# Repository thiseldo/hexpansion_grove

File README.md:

# "Seeed Studio Grove" connector adapter

Enables many of the [Grove expansion modules](https://wiki.seeedstudio.com/Grove_System/) to be used with the badge.

* I2C devices such as sensors
* I/O 1 uses HS_F and HS_G pins
* I/O 2 uses HS_H and HS_I pins

Use of pins is described at [Create a hexpansion](https://tildagon.badge.emfcamp.org/hexpansions/creating-hexpansions/)

# What's included

* kicad - The Kicad project files for the hexpansion along with gerbers ready to send to a PCB fabricator.
* software - Example applications for the hexpansions, using DS18B20 temperature probe and a Grove alcohol gas sensor.

## Acknowledgements

Uses the [hexpansion template from EMF](https://github.com/emfcamp/badge-2024-hardware/tree/main/hexpansion).

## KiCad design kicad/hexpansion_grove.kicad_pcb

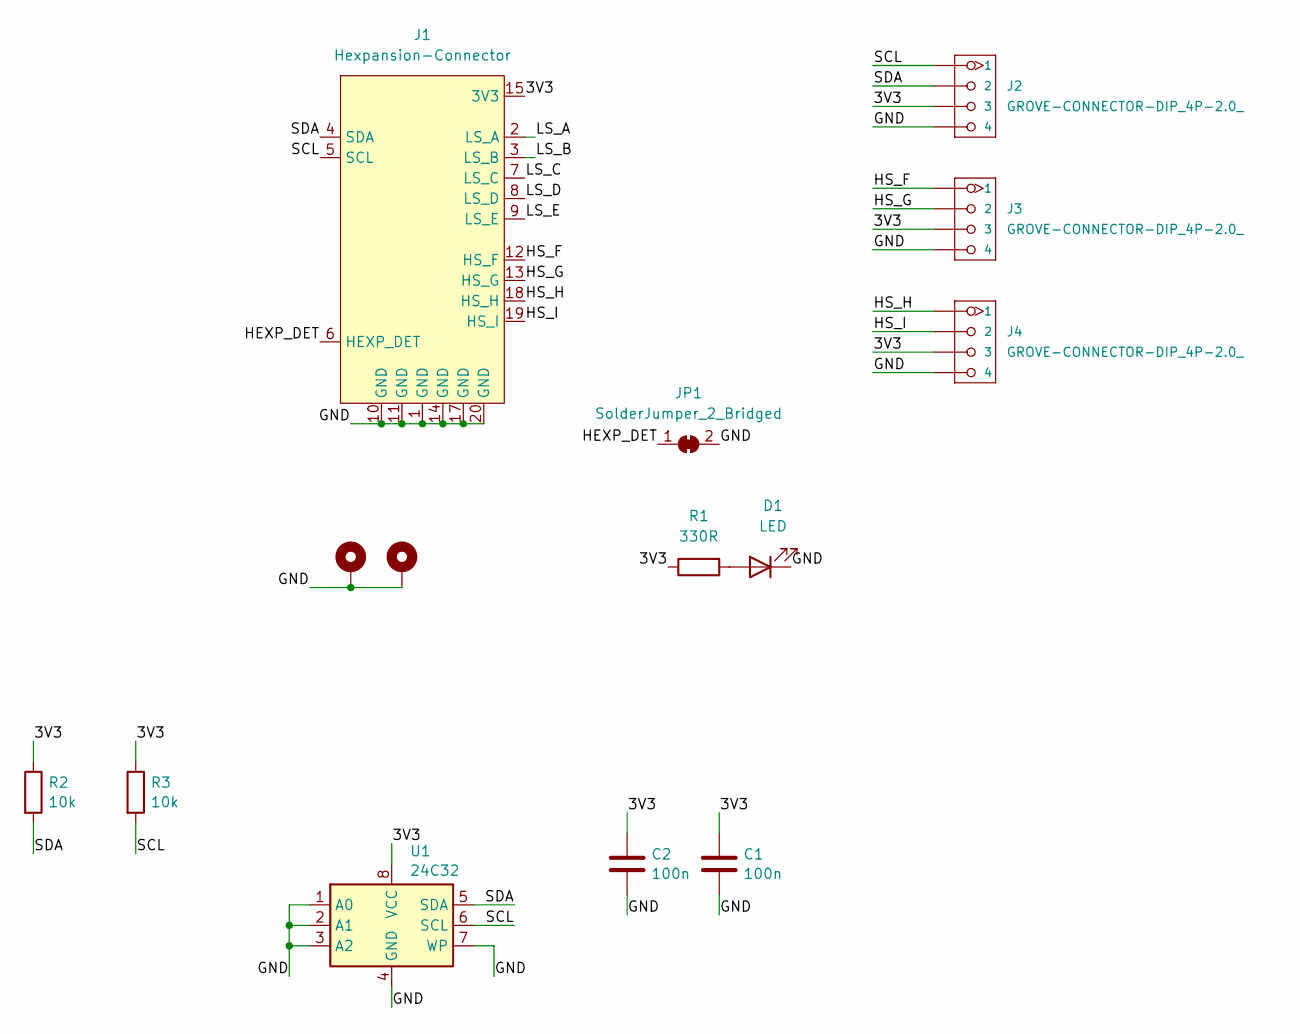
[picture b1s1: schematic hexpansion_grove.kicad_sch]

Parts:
C1, C2: 100n; C_0805_2012Metric_Pad1.18x1.45mm_HandSolder
D1: LED; LED_0805_2012Metric
H1, H2: MountingHole_Pad; MountingHole_2.2mm_M2_Pad_Via
J1: Hexpansion-Connector; hexpansion-edge-connector
J2, J3, J4: GROVE-CONNECTOR-DIP_4P-2.0_; GROVE-HW4-2.0
JP1: SolderJumper_2_Bridged; SolderJumper-2_P1.3mm_Bridged_RoundedPad1.0x1.5mm
R1: 330R; R_0805_2012Metric_Pad1.20x1.40mm_HandSolder
R2, R3: 10k; R_0805_2012Metric_Pad1.20x1.40mm_HandSolder
U1: 24C32; SOIC-8_3.9x4.9mm_P1.27mm

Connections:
/3V3: C1.1, C2.1, J1.15 (3V3), J1.16 (3V3), J2.3, J3.3, J4.3, R1.1, R2.1, R3.1, U1.8 (VCC)
/GND: C1.2, C2.2, D1.1 (K), H1.1, H2.1, J1.1 (GND), J1.10 (GND), J1.11 (GND), J1.14 (GND), J1.17 (GND), J1.20 (GND), J2.4, J3.4, J4.4, JP1.2 (B), U1.1 (A0), U1.2 (A1), U1.3 (A2), U1.4 (GND), U1.7 (WP)
/HEXP_DET: J1.6 (HEXP_DET), JP1.1 (A)
/HS_F: J1.12 (HS_F), J3.1
/HS_G: J1.13 (HS_G), J3.2
/HS_H: J1.18 (HS_H), J4.1
/HS_I: J1.19 (HS_I), J4.2
/LS_A: J1.2 (LS_A)
/LS_B: J1.3 (LS_B)
/LS_C: J1.7 (LS_C)
/LS_D: J1.8 (LS_D)
/LS_E: J1.9 (LS_E)
/SCL: J1.5 (SCL), J2.1, R3.2, U1.6 (SCL)
/SDA: J1.4 (SDA), J2.2, R2.2, U1.5 (SDA)
unnamed: D1.2 (A), R1.2

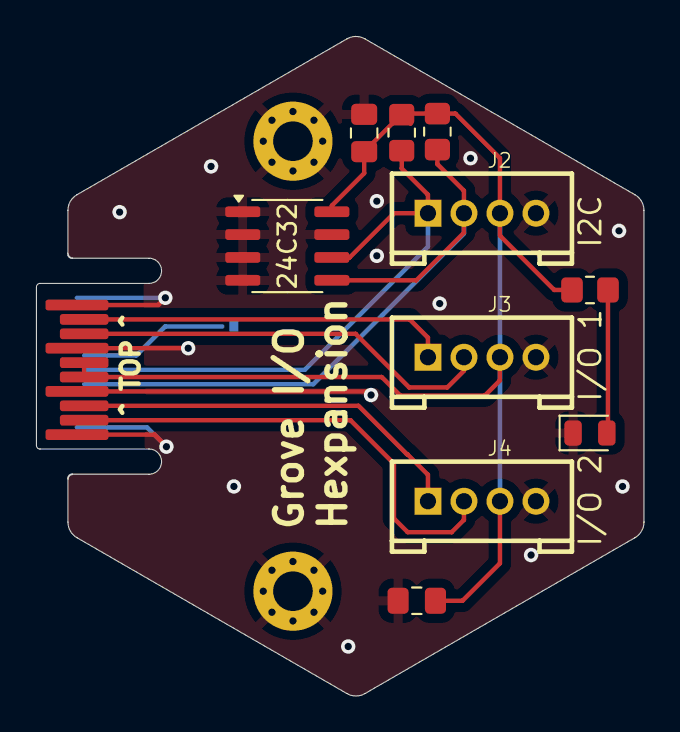
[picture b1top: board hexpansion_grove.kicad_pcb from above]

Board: 2 copper layers, 33.7 x 36.6 mm, 14 parts (1 on the bottom side), 10 nets.

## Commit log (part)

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2026-06-29 Update README with included files and examples
    Added details about included files and example applications for hexpansion.
